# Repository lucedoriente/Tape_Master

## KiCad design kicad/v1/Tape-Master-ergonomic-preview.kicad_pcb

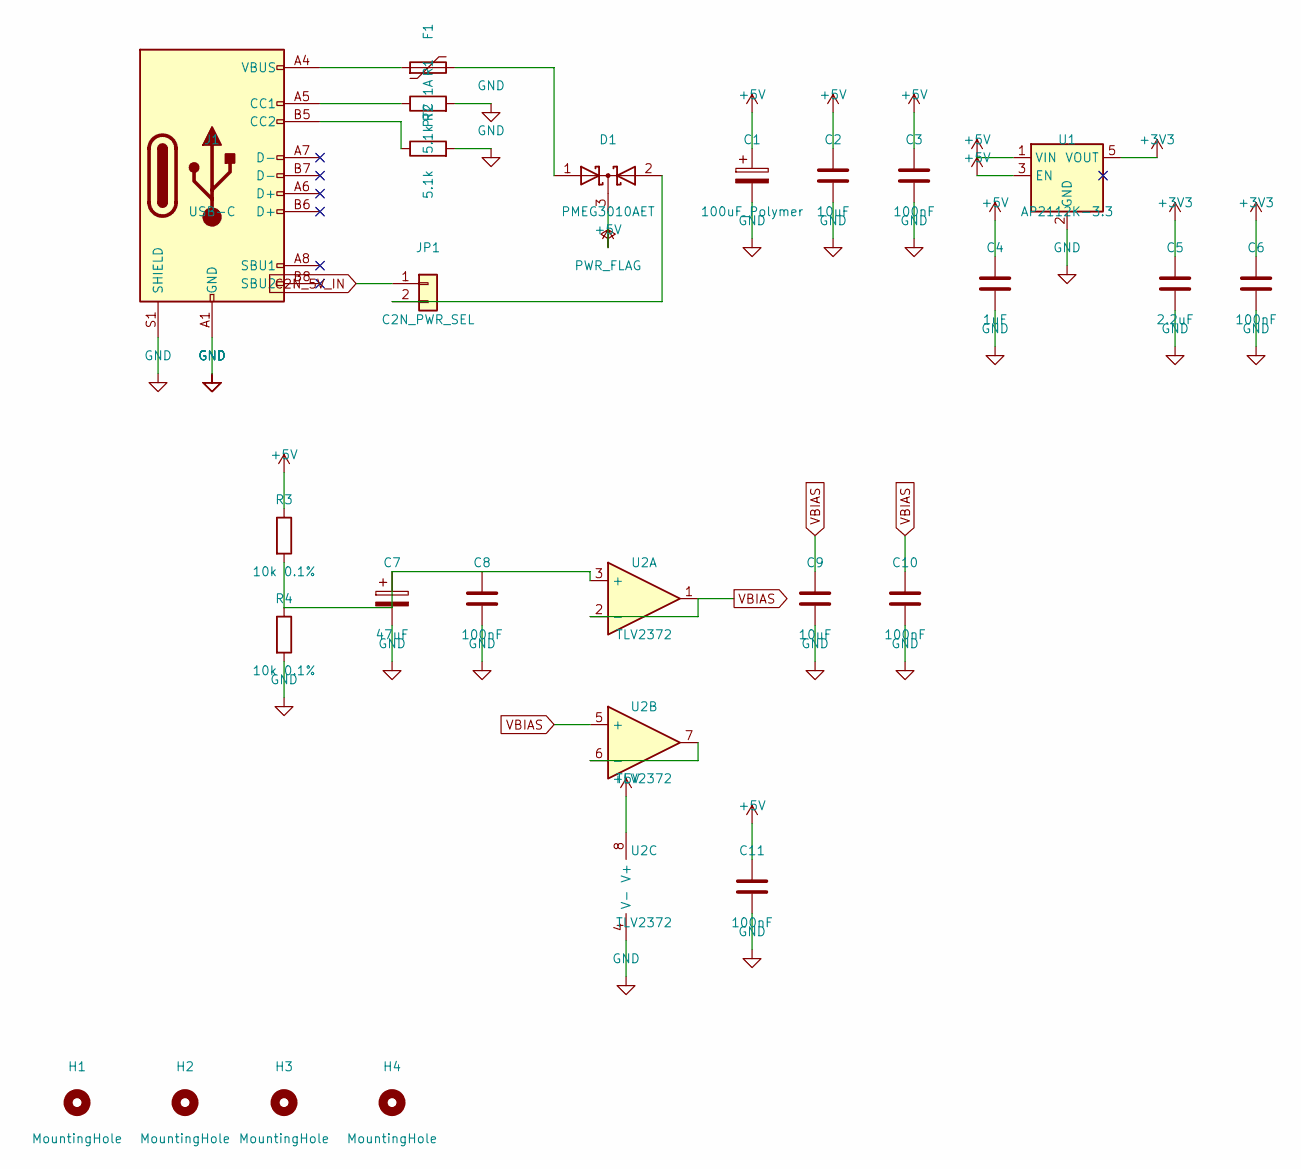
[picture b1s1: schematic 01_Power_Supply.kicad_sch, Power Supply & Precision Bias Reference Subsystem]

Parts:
C1: 100uF_Polymer; CP_EIA-3528-21_Kemet-B
C2, C9: 10uF; C_0805_2012Metric
C3, C6, C8, C10, C11: 100nF; C_0805_2012Metric
C4: 1uF; C_0805_2012Metric
C5: 2.2uF; C_0805_2012Metric
C7: 47uF; CP_EIA-3528-21_Kemet-B
D1: PMEG3010AET; SOT-23
F1: PTC 1A; Fuse_1206_3216Metric
H1, H2, H3, H4: MountingHole; MountingHole_3.2mm_M3
J1: USB-C; USB_C_Receptacle_GCT_USB4105-xx-A_16P_TopMnt_Horizontal
JP1: C2N_PWR_SEL; PinHeader_1x02_P2.54mm_Vertical
R1, R2: 5.1k; R_0805_2012Metric
R3, R4: 10k 0.1%; R_0805_2012Metric
U1: AP2112K-3.3; SOT-23-5
U2: TLV2372; SOIC-8_3.9x4.9mm_P1.27mm

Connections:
unnamed: D1.1 (A), F1.2
unnamed: F1.1, J1.A4 (VBUS), J1.A9 (VBUS), J1.B4 (VBUS), J1.B9 (VBUS)
unnamed: J1.A5 (CC1), R1.1
unnamed: J1.B5 (CC2), R2.1
unnamed: D1.2 (A), JP1.2
unnamed: C7.1, C8.1, R3.2, R4.1, U2.3 (+)
unnamed: U2.6 (-), U2.7
VBIAS: C9.1, C10.1, U2.1, U2.2 (-), U2.5 (+); also elsewhere on the board

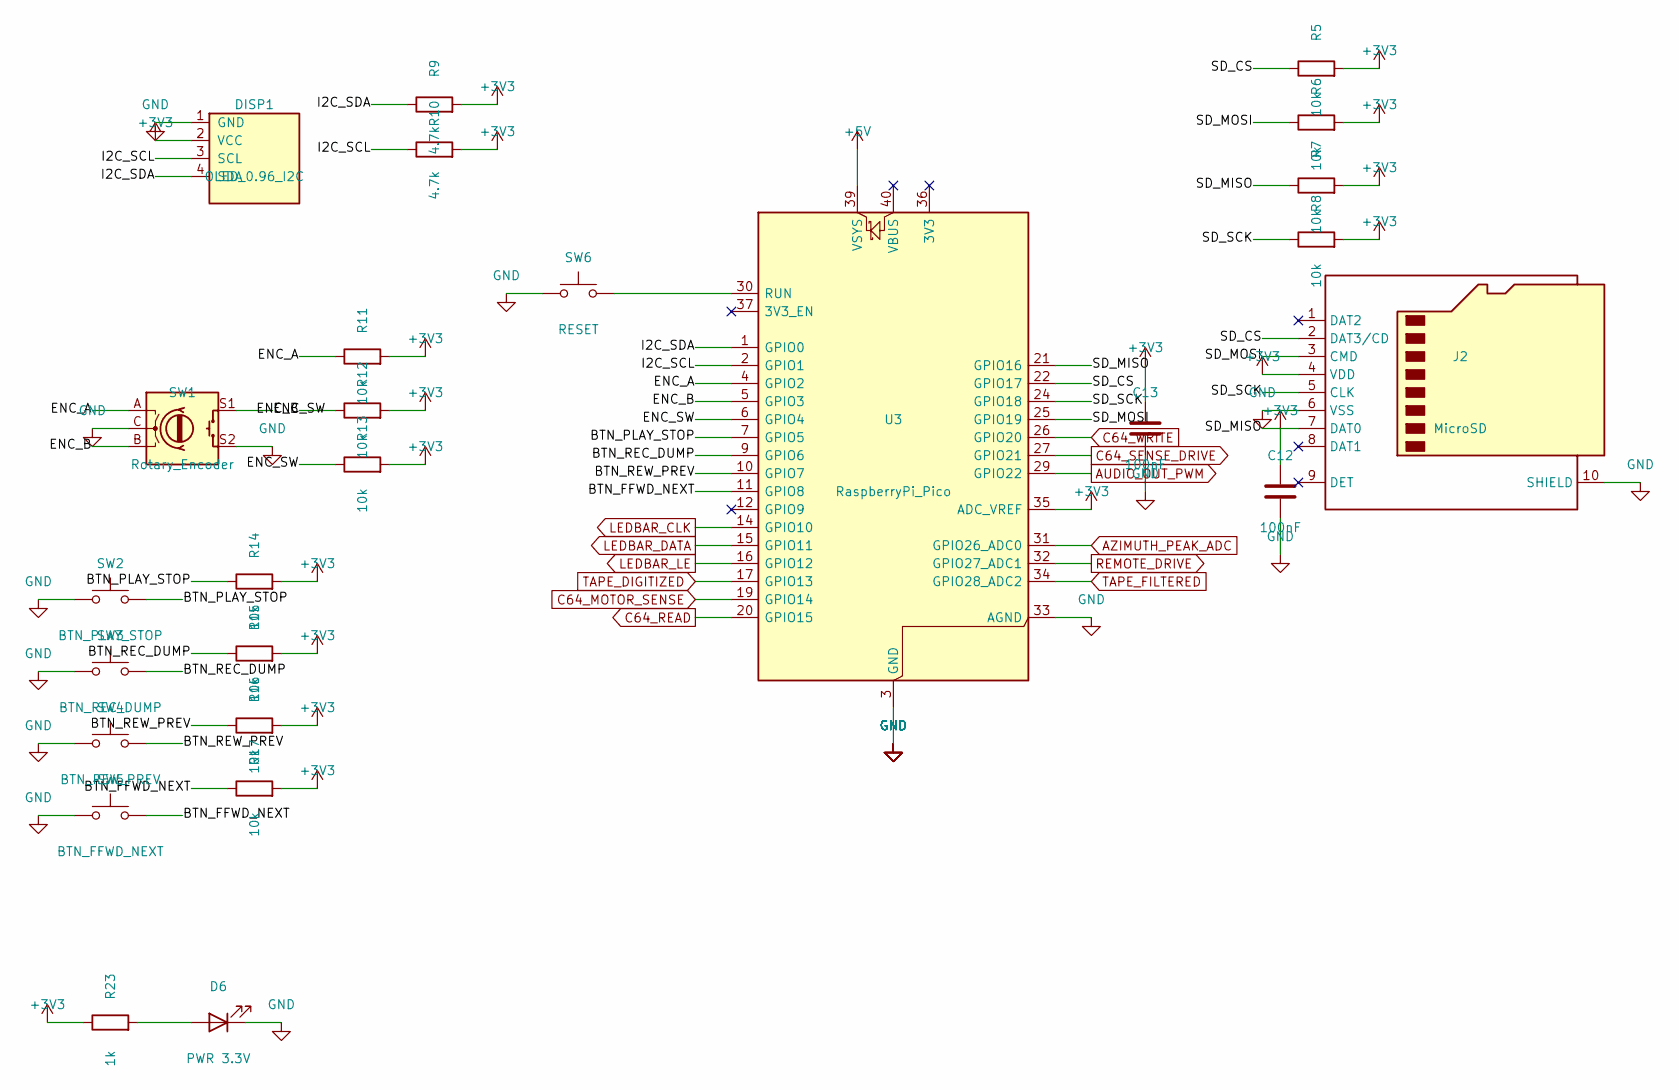
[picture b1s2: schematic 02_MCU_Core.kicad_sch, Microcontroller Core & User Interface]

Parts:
C12, C13: 100nF; C_0805_2012Metric
D6: PWR 3.3V; LED_0805_2012Metric
DISP1: OLED_0.96_I2C; PinHeader_1x04_P2.54mm_Vertical
J2: MicroSD; microSD_HC_Hirose_DM3D-SF
R5, R6, R7, R8, R11, R12, R13, R14, R15, R16, R17: 10k; R_0805_2012Metric
R9, R10: 4.7k; R_0805_2012Metric
R23: 1k; R_0805_2012Metric
SW1: Rotary_Encoder; RotaryEncoder_Alps_EC11E-Switch_Vertical_H20mm
SW2: BTN_PLAY_STOP; SW_PUSH_6mm
SW3: BTN_REC_DUMP; SW_PUSH_6mm
SW4: BTN_REW_PREV; SW_PUSH_6mm
SW5: BTN_FFWD_NEXT; SW_PUSH_6mm
SW6: RESET; SW_PUSH_6mm
U3: RaspberryPi_Pico; RaspberryPi_Pico_Common_THT

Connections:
/02_MCU_Core/BTN_FFWD_NEXT: R17.1, SW5.2, U3.11 (GPIO8)
/02_MCU_Core/BTN_PLAY_STOP: R14.1, SW2.2, U3.7 (GPIO5)
/02_MCU_Core/BTN_REC_DUMP: R15.1, SW3.2, U3.9 (GPIO6)
/02_MCU_Core/BTN_REW_PREV: R16.1, SW4.2, U3.10 (GPIO7)
/02_MCU_Core/ENC_A: R11.1, SW1.A, U3.4 (GPIO2)
/02_MCU_Core/ENC_B: R12.1, SW1.B, U3.5 (GPIO3)
/02_MCU_Core/ENC_SW: R13.1, SW1.S1, U3.6 (GPIO4)
/02_MCU_Core/I2C_SCL: DISP1.3 (SCL), R10.1, U3.2 (GPIO1)
/02_MCU_Core/I2C_SDA: DISP1.4 (SDA), R9.1, U3.1 (GPIO0)
/02_MCU_Core/SD_CS: J2.2 (DAT3/CD), R5.1, U3.22 (GPIO17)
/02_MCU_Core/SD_MOSI: J2.3 (CMD), R6.1, U3.25 (GPIO19)
/02_MCU_Core/SD_SCK: J2.5 (CLK), R8.1, U3.24 (GPIO18)
AUDIO_OUT_PWM: U3.29 (GPIO22); also elsewhere on the board
C64_MOTOR_SENSE: U3.19 (GPIO14); also elsewhere on the board
C64_READ: U3.20 (GPIO15); also elsewhere on the board
C64_SENSE_DRIVE: U3.27 (GPIO21); also elsewhere on the board
C64_WRITE: U3.26 (GPIO20); also elsewhere on the board
LEDBAR_CLK: U3.14 (GPIO10); also elsewhere on the board
LEDBAR_DATA: U3.15 (GPIO11); also elsewhere on the board
LEDBAR_LE: U3.16 (GPIO12); also elsewhere on the board
unnamed: D6.2 (A), R23.2
unnamed: SW6.2, U3.30 (RUN)
REMOTE_DRIVE: U3.32 (GPIO27_ADC1); also elsewhere on the board
TAPE_DIGITIZED: U3.17 (GPIO13); also elsewhere on the board
TAPE_FILTERED: U3.34 (GPIO28_ADC2); also elsewhere on the board

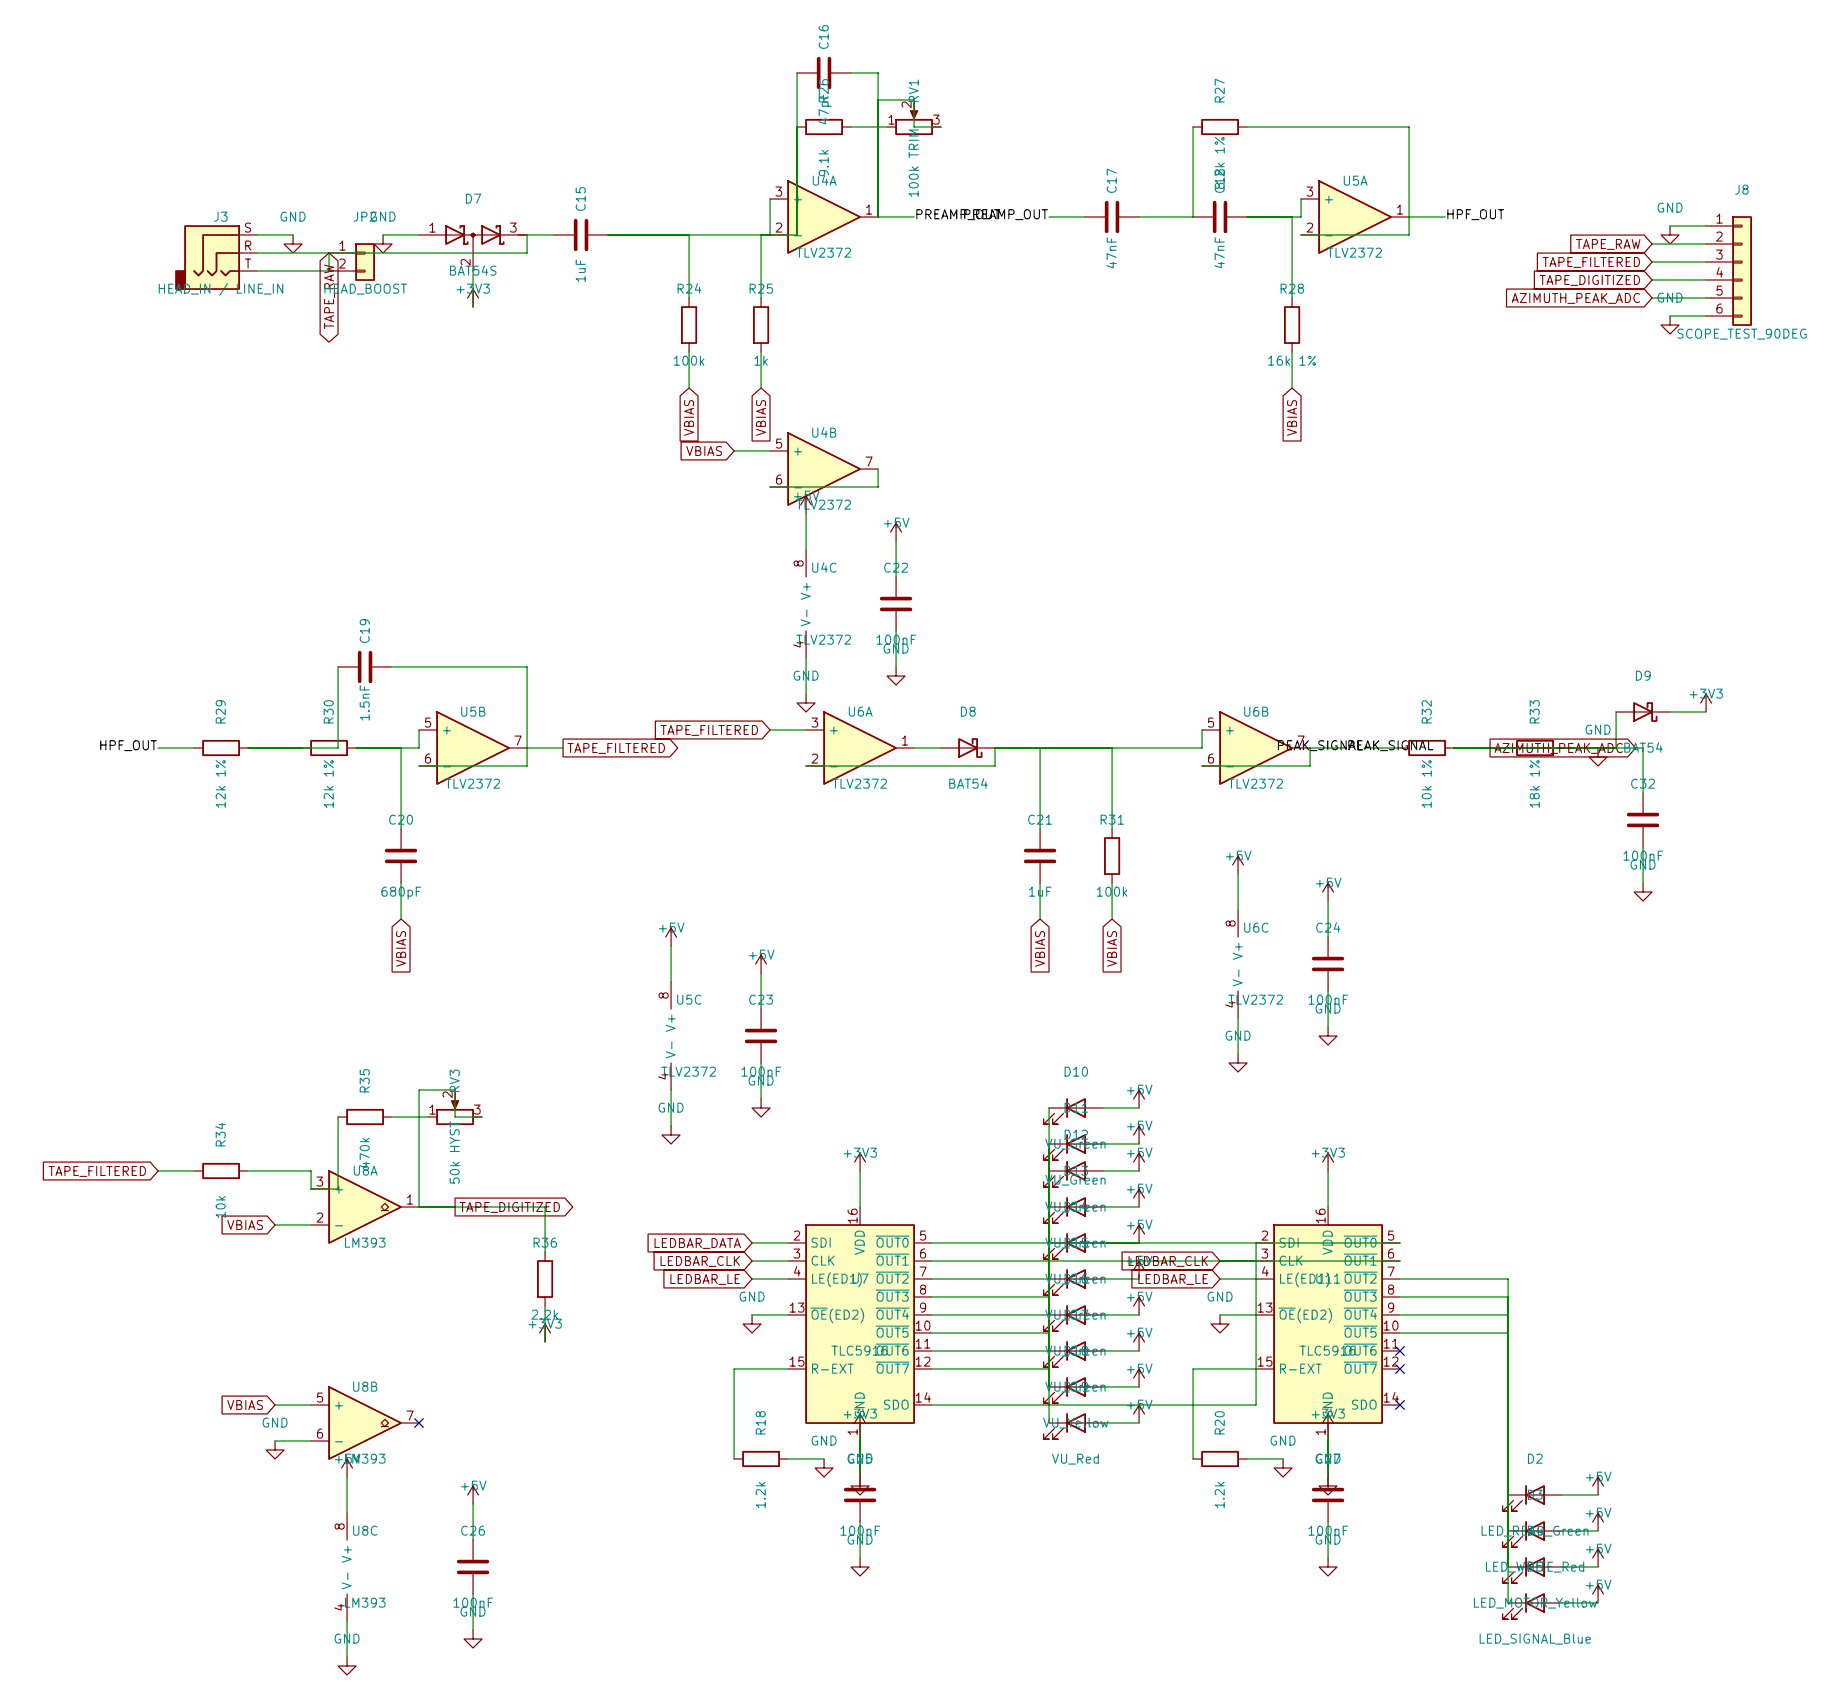
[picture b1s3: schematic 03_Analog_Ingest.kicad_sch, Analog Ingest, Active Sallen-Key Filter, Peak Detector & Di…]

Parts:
C15, C21: 1uF; C_0805_2012Metric
C16: 47pF; C_0805_2012Metric
C17, C18: 47nF; C_0805_2012Metric
C19: 1.5nF; C_0805_2012Metric
C20: 680pF; C_0805_2012Metric
C22, C23, C24, C25, C26, C27, C32: 100nF; C_0805_2012Metric
D2: LED_READ_Green; LED_0805_2012Metric
D3: LED_WRITE_Red; LED_0805_2012Metric
D4: LED_MOTOR_Yellow; LED_0805_2012Metric
D5: LED_SIGNAL_Blue; LED_0805_2012Metric
D7: BAT54S; SOT-23
D8, D9: BAT54; SOT-23
D10, D11, D12, D13, D14, D15, D16, D17: VU_Green; LED_0805_2012Metric
D18: VU_Yellow; LED_0805_2012Metric
D19: VU_Red; LED_0805_2012Metric
J3: HEAD_IN / LINE_IN; Jack_3.5mm_CUI_SJ-3523-SMT_Horizontal
J8: SCOPE_TEST_90DEG; PinHeader_1x06_P2.54mm_Horizontal
JP2: HEAD_BOOST; PinHeader_1x02_P2.54mm_Vertical
R18, R20: 1.2k; R_0805_2012Metric
R24, R31: 100k; R_0805_2012Metric
R25: 1k; R_0805_2012Metric
R26: 9.1k; R_0805_2012Metric
R27: 8.2k 1%; R_0805_2012Metric
R28: 16k 1%; R_0805_2012Metric
R29, R30: 12k 1%; R_0805_2012Metric
R32: 10k 1%; R_0805_2012Metric
R33: 18k 1%; R_0805_2012Metric
R34: 10k; R_0805_2012Metric
R35: 470k; R_0805_2012Metric
R36: 2.2k; R_0805_2012Metric
RV1: 100k TRIM; Potentiometer_Bourns_3296W_Vertical
RV3: 50k HYST; Potentiometer_Bourns_3296W_Vertical
U4, U5, U6: TLV2372; SOIC-8_3.9x4.9mm_P1.27mm
U7, U11: TLC5916; SOIC-16_3.9x9.9mm_P1.27mm
U8: LM393; SOIC-8_3.9x4.9mm_P1.27mm

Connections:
/03_Analog_Ingest/HPF_OUT: R27.2, R29.1, U5.1, U5.2 (-)
/03_Analog_Ingest/PEAK_SIGNAL: R32.1, U6.6 (-), U6.7
/03_Analog_Ingest/PREAMP_OUT: C16.2, C17.1, RV1.2, RV1.3, U4.1
LEDBAR_CLK: D11.1 (K), D19.1 (K), U7.3 (CLK), U7.6 (~OUT1), U11.3 (CLK), U11.6 (~OUT1); also elsewhere on the board
LEDBAR_DATA: U7.2 (SDI); also elsewhere on the board
LEDBAR_LE: U7.4 (LE(ED1)), U11.4 (LE(ED1)); also elsewhere on the board
unnamed: C17.2, C18.1, R27.1
unnamed: C19.1, R29.2, R30.1
unnamed: D2.1 (K), U11.7 (~OUT2)
unnamed: D3.1 (K), U11.8 (~OUT3)
unnamed: D4.1 (K), U11.9 (~OUT4)
unnamed: D5.1 (K), U11.10 (~OUT5)
unnamed: D8.2 (A), U6.1
unnamed: C21.1, D8.1 (K), R31.1, U6.2 (-), U6.5 (+)
unnamed: D12.1 (K), D15.1 (K), U7.7 (~OUT2), U7.10 (~OUT5)
unnamed: D13.1 (K), U7.8 (~OUT3)
unnamed: R26.2, RV1.1
unnamed: R35.2, RV3.1
unnamed: C15.2, C16.1, R24.1, R25.1, R26.1, U4.2 (-), U4.3 (+)
unnamed: U4.6 (-), U4.7
unnamed: C18.2, R28.1, U5.3 (+)
unnamed: C20.1, R30.2, U5.5 (+)
unnamed: R18.1, U7.15 (R-EXT)
unnamed: R34.2, R35.1, U8.3 (+)
unnamed: R20.1, U11.15 (R-EXT)
unnamed: U7.14 (SDO), U11.2 (SDI)
TAPE_DIGITIZED: J8.4, R36.1, RV3.2, RV3.3, U8.1; also elsewhere on the board
TAPE_FILTERED: C19.2, J8.3, R34.1, U5.6 (-), U5.7, U6.3 (+); also elsewhere on the board
TAPE_RAW: C15.1, D7.3 (K), J3.R, J3.T, J8.2, JP2.1, JP2.2
VBIAS: C20.2, C21.2, R24.2, R25.2, R28.2, R31.2, U4.5 (+), U8.2 (-), U8.5 (+); also elsewhere on the board

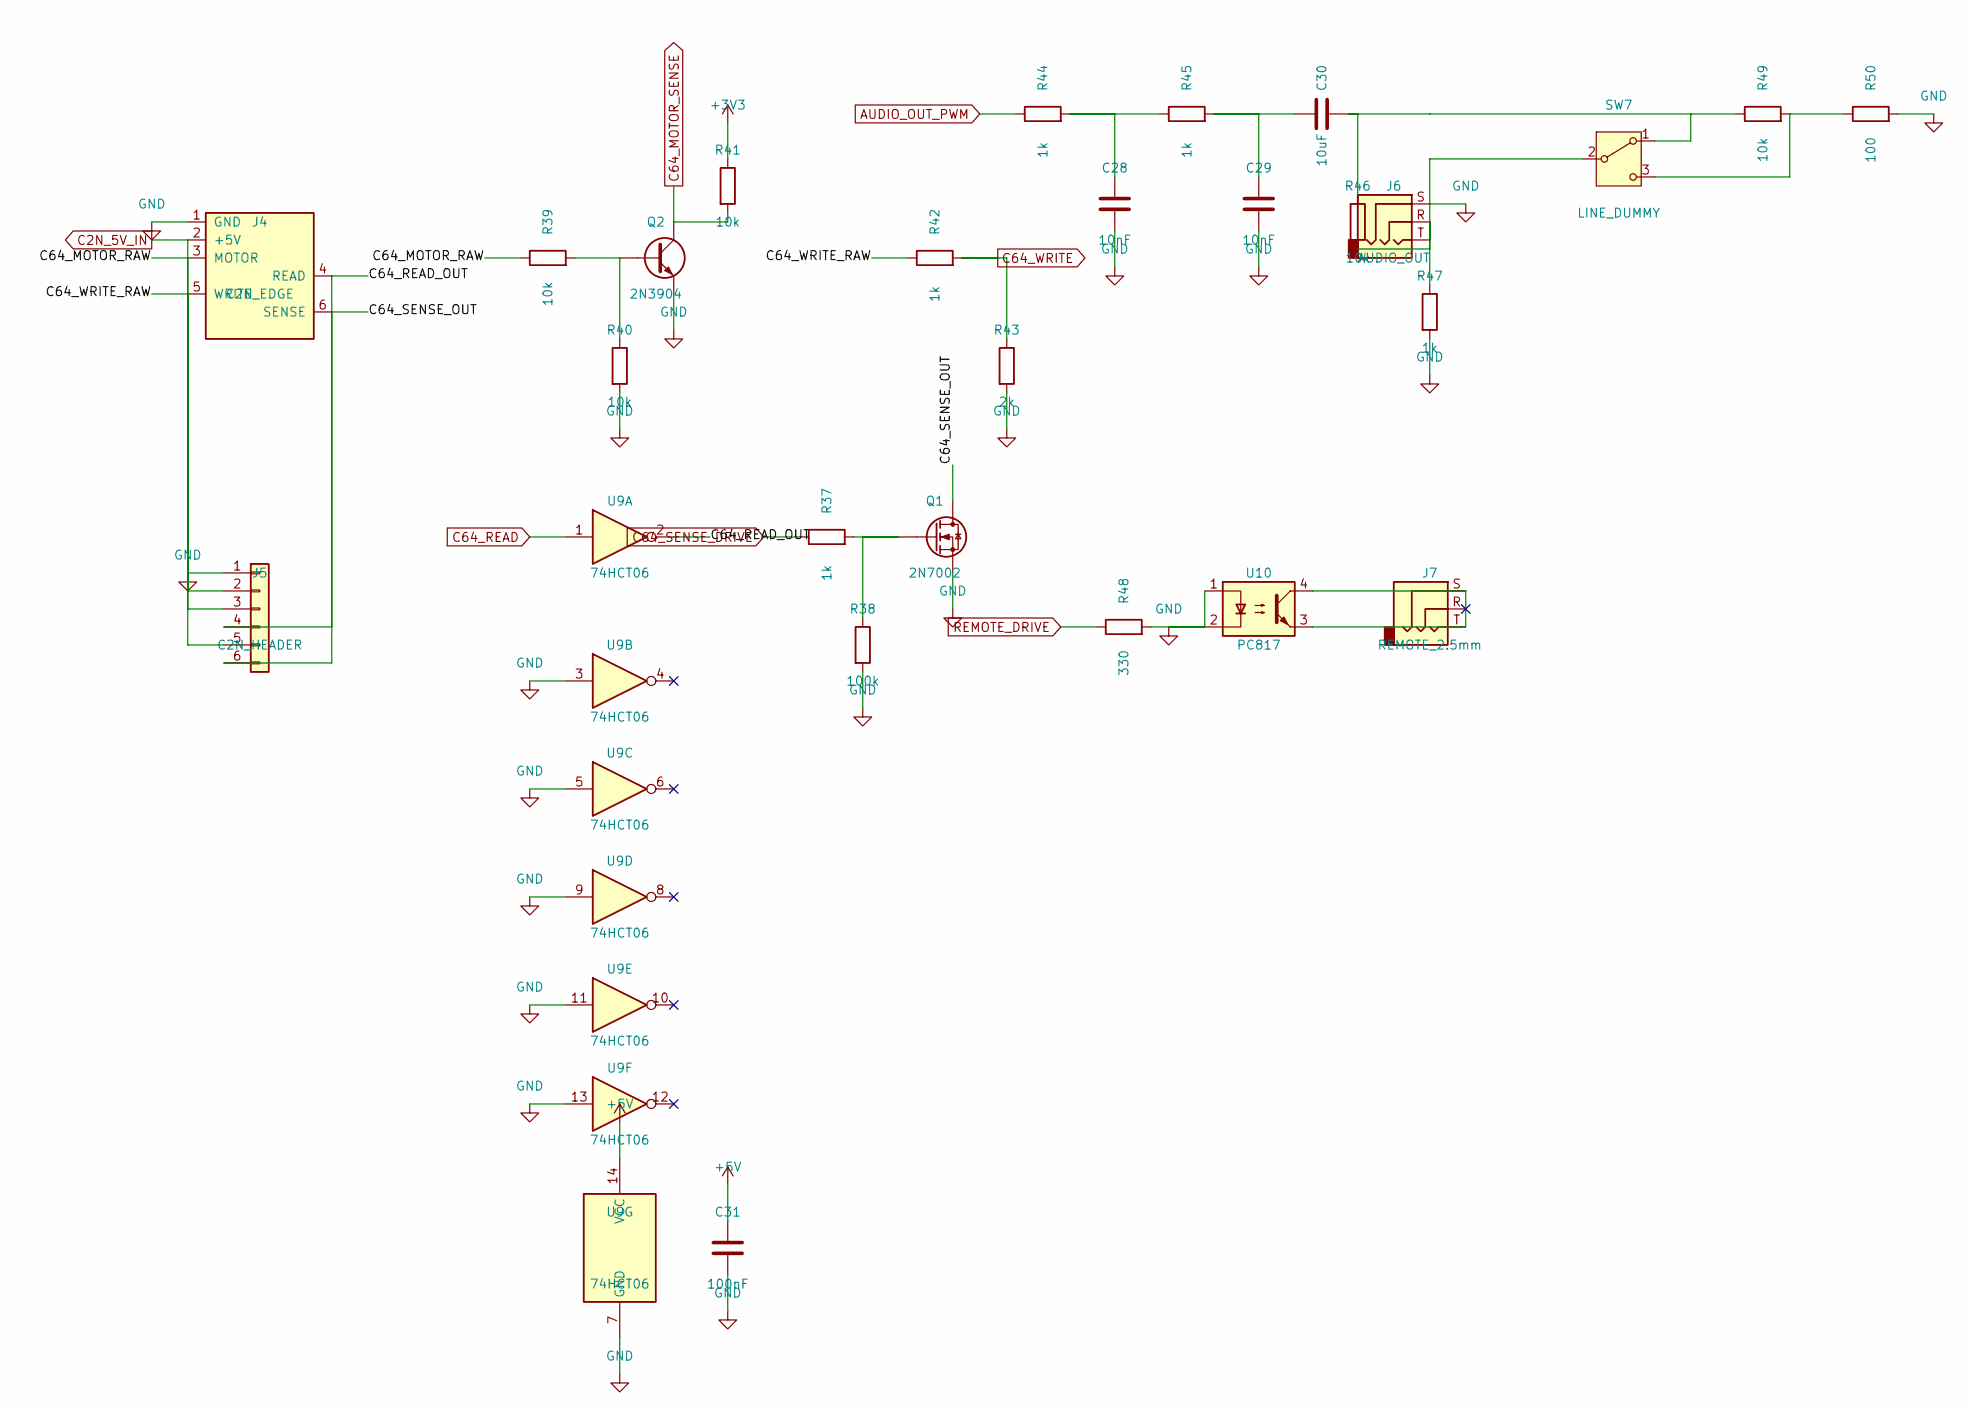
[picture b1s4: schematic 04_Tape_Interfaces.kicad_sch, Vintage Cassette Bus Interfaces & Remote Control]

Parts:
C28, C29: 10nF; C_0805_2012Metric
C30: 10uF; C_0805_2012Metric
C31: 100nF; C_0805_2012Metric
J4: C2N_EDGE; C2N_Edge_Connector
J5: C2N_HEADER; PinHeader_1x06_P2.54mm_Horizontal
J6: AUDIO_OUT; Jack_3.5mm_CUI_SJ-3523-SMT_Horizontal
J7: REMOTE_2.5mm; Jack_3.5mm_CUI_SJ-3523-SMT_Horizontal
Q1: 2N7002; SOT-23
Q2: 2N3904; SOT-23
R37, R42, R44, R45, R47: 1k; R_0805_2012Metric
R38: 100k; R_0805_2012Metric
R39, R40, R41, R46, R49: 10k; R_0805_2012Metric
R43: 2k; R_0805_2012Metric
R48: 330; R_0805_2012Metric
R50: 100; R_0805_2012Metric
SW7: LINE_DUMMY; SW_Slide_SPDT_Straight_CK_OS102011MS2Q
U9: 74HCT06; SOIC-14_3.9x8.7mm_P1.27mm
U10: PC817; DIP-4_W7.62mm

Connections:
/04_Tape_Interfaces/C64_READ_OUT: J4.4 (READ), J5.4, U9.2
/04_Tape_Interfaces/C64_SENSE_OUT: J4.6 (SENSE), J5.6, Q1.3 (D)
AUDIO_OUT_PWM: R44.1; also elsewhere on the board
C64_MOTOR_SENSE: Q2.3 (C), R41.2; also elsewhere on the board
C64_READ: U9.1; also elsewhere on the board
C64_SENSE_DRIVE: R37.1; also elsewhere on the board
C64_WRITE: R42.2, R43.1; also elsewhere on the board
unnamed: C28.1, R44.2, R45.1
unnamed: C29.1, C30.1, R45.2
unnamed: J6.R, R46.2, R47.1
unnamed: J7.S, J7.T, U10.3, U10.4
unnamed: Q1.1 (G), R37.2, R38.1
unnamed: Q2.1 (B), R39.2, R40.1
unnamed: C30.2, R46.1, R49.1, SW7.1 (A)
unnamed: J6.T, SW7.2 (B)
unnamed: R49.2, R50.1, SW7.3 (C)
REMOTE_DRIVE: R48.1; also elsewhere on the board

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
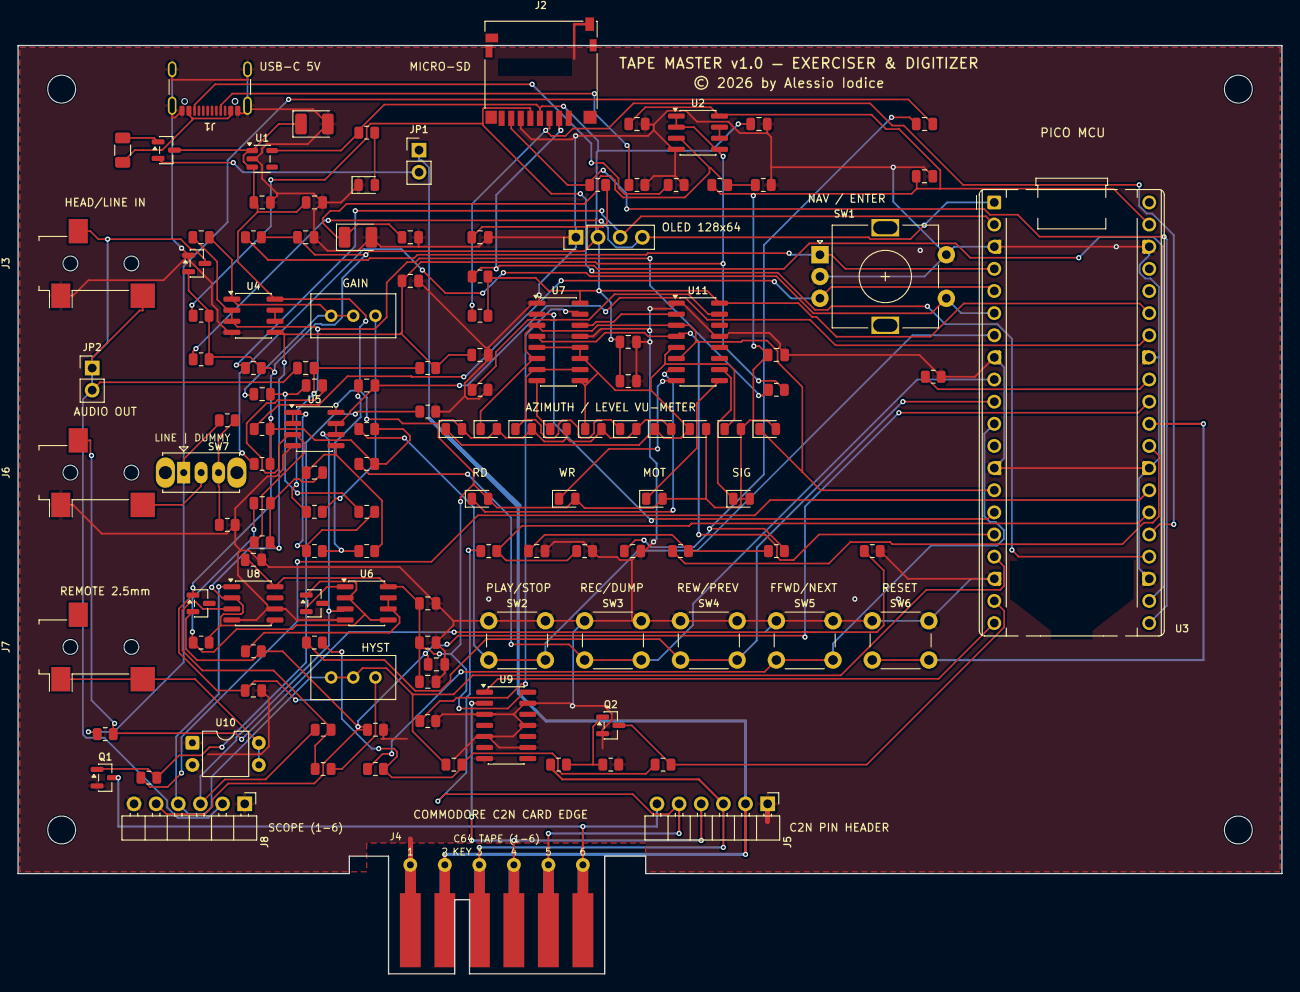
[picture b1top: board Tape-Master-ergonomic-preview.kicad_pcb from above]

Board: 2 copper layers, 145.0 x 106.5 mm, 135 parts (0 on the bottom side), 77 nets.

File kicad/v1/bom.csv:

"Refs","Value","Footprint","Qty","DNP"
"C1","100uF_Polymer","Capacitor_Tantalum_SMD:CP_EIA-3528-21_Kemet-B","1",""
"C2","10uF","Capacitor_SMD:C_0805_2012Metric","1",""
"C3","100nF","Capacitor_SMD:C_0805_2012Metric","1",""
"C4","1uF","Capacitor_SMD:C_0805_2012Metric","1",""
"C5","2.2uF","Capacitor_SMD:C_0805_2012Metric","1",""
"C6","100nF","Capacitor_SMD:C_0805_2012Metric","1",""
"C7","47uF","Capacitor_Tantalum_SMD:CP_EIA-3528-21_Kemet-B","1",""
"C8","100nF","Capacitor_SMD:C_0805_2012Metric","1",""
"C9","10uF","Capacitor_SMD:C_0805_2012Metric","1",""
"C10","100nF","Capacitor_SMD:C_0805_2012Metric","1",""
"C11","100nF","Capacitor_SMD:C_0805_2012Metric","1",""
"C12","100nF","Capacitor_SMD:C_0805_2012Metric","1",""
"C13","100nF","Capacitor_SMD:C_0805_2012Metric","1",""
"C15","1uF","Capacitor_SMD:C_0805_2012Metric","1",""
"C16","47pF","Capacitor_SMD:C_0805_2012Metric","1",""
"C17","47nF","Capacitor_SMD:C_0805_2012Metric","1",""
"C18","47nF","Capacitor_SMD:C_0805_2012Metric","1",""
"C19","1.5nF","Capacitor_SMD:C_0805_2012Metric","1",""
"C20","680pF","Capacitor_SMD:C_0805_2012Metric","1",""
"C21","1uF","Capacitor_SMD:C_0805_2012Metric","1",""
"C22","100nF","Capacitor_SMD:C_0805_2012Metric","1",""
"C23","100nF","Capacitor_SMD:C_0805_2012Metric","1",""
"C24","100nF","Capacitor_SMD:C_0805_2012Metric","1",""
"C25","100nF","Capacitor_SMD:C_0805_2012Metric","1",""
"C26","100nF","Capacitor_SMD:C_0805_2012Metric","1",""
"C27","100nF","Capacitor_SMD:C_0805_2012Metric","1",""
"C28","10nF","Capacitor_SMD:C_0805_2012Metric","1",""
"C29","10nF","Capacitor_SMD:C_0805_2012Metric","1",""
"C30","10uF","Capacitor_SMD:C_0805_2012Metric","1",""
"C31","100nF","Capacitor_SMD:C_0805_2012Metric","1",""
"C32","100nF","Capacitor_SMD:C_0805_2012Metric","1",""
"D1","PMEG3010AET","Package_TO_SOT_SMD:SOT-23","1",""
"D2","LED_READ_Green","LED_SMD:LED_0805_2012Metric","1",""
"D3","LED_WRITE_Red","LED_SMD:LED_0805_2012Metric","1",""
"D4","LED_MOTOR_Yellow","LED_SMD:LED_0805_2012Metric","1",""
"D5","LED_SIGNAL_Blue","LED_SMD:LED_0805_2012Metric","1",""
"D6","PWR 3.3V","LED_SMD:LED_0805_2012Metric","1",""
"D7","BAT54S","Package_TO_SOT_SMD:SOT-23","1",""
"D8","BAT54","Package_TO_SOT_SMD:SOT-23","1",""
"D9","BAT54","Package_TO_SOT_SMD:SOT-23","1",""
"D10","VU_Green","LED_SMD:LED_0805_2012Metric","1",""
"D11","VU_Green","LED_SMD:LED_0805_2012Metric","1",""
"D12","VU_Green","LED_SMD:LED_0805_2012Metric","1",""
"D13","VU_Green","LED_SMD:LED_0805_2012Metric","1",""
"D14","VU_Green","LED_SMD:LED_0805_2012Metric","1",""
"D15","VU_Green","LED_SMD:LED_0805_2012Metric","1",""
"D16","VU_Green","LED_SMD:LED_0805_2012Metric","1",""
"D17","VU_Green","LED_SMD:LED_0805_2012Metric","1",""
"D18","VU_Yellow","LED_SMD:LED_0805_2012Metric","1",""
"D19","VU_Red","LED_SMD:LED_0805_2012Metric","1",""
"DISP1","OLED_0.96_I2C","Connector_PinHeader_2.54mm:PinHeader_1x04_P2.54mm_Vertical","1",""
"F1","PTC 1A","Fuse:Fuse_1206_3216Metric","1",""
"H1","MountingHole","MountingHole:MountingHole_3.2mm_M3","1",""
"H2","MountingHole","MountingHole:MountingHole_3.2mm_M3","1",""
"H3","MountingHole","MountingHole:MountingHole_3.2mm_M3","1",""
"H4","MountingHole","MountingHole:MountingHole_3.2mm_M3","1",""
"J1","USB-C","Connector_USB:USB_C_Receptacle_GCT_USB4105-xx-A_16P_TopMnt_Horizontal","1",""
"J2","MicroSD","Connector_Card:microSD_HC_Hirose_DM3D-SF","1",""
"J3","HEAD_IN / LINE_IN","Connector_Audio:Jack_3.5mm_CUI_SJ-3523-SMT_Horizontal","1",""
"J4","C2N_EDGE","Tape-Master:C2N_Edge_Connector","1",""
"J5","C2N_HEADER","Connector_PinHeader_2.54mm:PinHeader_1x06_P2.54mm_Vertical","1",""
"J6","AUDIO_OUT","Connector_Audio:Jack_3.5mm_CUI_SJ-3523-SMT_Horizontal","1",""
"J7","REMOTE_2.5mm","Connector_Audio:Jack_3.5mm_CUI_SJ-3523-SMT_Horizontal","1",""
"JP1","C2N_PWR_SEL","Connector_PinHeader_2.54mm:PinHeader_1x02_P2.54mm_Vertical","1",""
"JP2","HEAD_BOOST","Connector_PinHeader_2.54mm:PinHeader_1x02_P2.54mm_Vertical","1",""
"Q1","2N7002","Package_TO_SOT_SMD:SOT-23","1",""
"Q2","2N3904","Package_TO_SOT_SMD:SOT-23","1",""
"R1","5.1k","Resistor_SMD:R_0805_2012Metric","1",""
"R2","5.1k","Resistor_SMD:R_0805_2012Metric","1",""
"R3","10k 0.1%","Resistor_SMD:R_0805_2012Metric","1",""
"R4","10k 0.1%","Resistor_SMD:R_0805_2012Metric","1",""
"R5","10k","Resistor_SMD:R_0805_2012Metric","1",""
"R6","10k","Resistor_SMD:R_0805_2012Metric","1",""
"R7","10k","Resistor_SMD:R_0805_2012Metric","1",""
"R8","10k","Resistor_SMD:R_0805_2012Metric","1",""
"R9","4.7k","Resistor_SMD:R_0805_2012Metric","1",""
"R10","4.7k","Resistor_SMD:R_0805_2012Metric","1",""
"R11","10k","Resistor_SMD:R_0805_2012Metric","1",""
"R12","10k","Resistor_SMD:R_0805_2012Metric","1",""
"R13","10k","Resistor_SMD:R_0805_2012Metric","1",""
"R14","10k","Resistor_SMD:R_0805_2012Metric","1",""
"R15","10k","Resistor_SMD:R_0805_2012Metric","1",""
"R16","10k","Resistor_SMD:R_0805_2012Metric","1",""
"R17","10k","Resistor_SMD:R_0805_2012Metric","1",""
"R18","1.2k","Resistor_SMD:R_0805_2012Metric","1",""
"R20","1.2k","Resistor_SMD:R_0805_2012Metric","1",""
"R23","1k","Resistor_SMD:R_0805_2012Metric","1",""
"R24","100k","Resistor_SMD:R_0805_2012Metric","1",""
"R25","1k","Resistor_SMD:R_0805_2012Metric","1",""
"R26","9.1k","Resistor_SMD:R_0805_2012Metric","1",""
"R27","8.2k 1%","Resistor_SMD:R_0805_2012Metric","1",""
"R28","16k 1%","Resistor_SMD:R_0805_2012Metric","1",""
"R29","12k 1%","Resistor_SMD:R_0805_2012Metric","1",""
"R30","12k 1%","Resistor_SMD:R_0805_2012Metric","1",""
"R31","100k","Resistor_SMD:R_0805_2012Metric","1",""
"R32","10k 1%","Resistor_SMD:R_0805_2012Metric","1",""
"R33","18k 1%","Resistor_SMD:R_0805_2012Metric","1",""
"R34","10k","Resistor_SMD:R_0805_2012Metric","1",""
"R35","470k","Resistor_SMD:R_0805_2012Metric","1",""
"R36","2.2k","Resistor_SMD:R_0805_2012Metric","1",""
"R37","1k","Resistor_SMD:R_0805_2012Metric","1",""
"R38","100k","Resistor_SMD:R_0805_2012Metric","1",""
"R39","10k","Resistor_SMD:R_0805_2012Metric","1",""
"R40","10k","Resistor_SMD:R_0805_2012Metric","1",""
"R41","10k","Resistor_SMD:R_0805_2012Metric","1",""
"R42","1k","Resistor_SMD:R_0805_2012Metric","1",""
"R43","2k","Resistor_SMD:R_0805_2012Metric","1",""
"R44","1k","Resistor_SMD:R_0805_2012Metric","1",""
"R45","1k","Resistor_SMD:R_0805_2012Metric","1",""
"R46","10k","Resistor_SMD:R_0805_2012Metric","1",""
"R47","1k","Resistor_SMD:R_0805_2012Metric","1",""
"R48","330","Resistor_SMD:R_0805_2012Metric","1",""
"RV1","100k TRIM","Potentiometer_THT:Potentiometer_Bourns_3296W_Vertical","1",""
"RV3","50k HYST","Potentiometer_THT:Potentiometer_Bourns_3296W_Vertical","1",""
"SW1","Rotary_Encoder","Rotary_Encoder:RotaryEncoder_Alps_EC11E-Switch_Vertical_H20mm","1",""
"SW2","BTN_PLAY_STOP","Button_Switch_THT:SW_PUSH_6mm","1",""
"SW3","BTN_REC_DUMP","Button_Switch_THT:SW_PUSH_6mm","1",""
"SW4","BTN_REW_PREV","Button_Switch_THT:SW_PUSH_6mm","1",""
"SW5","BTN_FFWD_NEXT","Button_Switch_THT:SW_PUSH_6mm","1",""
"SW6","RESET","Button_Switch_THT:SW_PUSH_6mm","1",""
"U1","AP2112K-3.3","Package_TO_SOT_SMD:SOT-23-5","1",""
"U2","TLV2372","Package_SO:SOIC-8_3.9x4.9mm_P1.27mm","1",""
"U3","RaspberryPi_Pico","Module:RaspberryPi_Pico_Common_THT","1",""
"U4","TLV2372","Package_SO:SOIC-8_3.9x4.9mm_P1.27mm","1",""
"U5","TLV2372","Package_SO:SOIC-8_3.9x4.9mm_P1.27mm","1",""
"U6","TLV2372","Package_SO:SOIC-8_3.9x4.9mm_P1.27mm","1",""
"U7","TLC5916","Package_SO:SOIC-16_3.9x9.9mm_P1.27mm","1",""
"U8","LM393","Package_SO:SOIC-8_3.9x4.9mm_P1.27mm","1",""
"U9","74HCT06","Package_SO:SOIC-14_3.9x8.7mm_P1.27mm","1",""
"U10","PC817","Package_DIP:DIP-4_W7.62mm","1",""
"U11","TLC5916","Package_SO:SOIC-16_3.9x9.9mm_P1.27mm","1",""

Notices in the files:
kicad/v1/01_Power_Supply.kicad_sch:
License: CC BY-NC-SA 4.0
